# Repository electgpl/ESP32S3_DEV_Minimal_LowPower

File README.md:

# ESP32S3_DEV_Minimal_LowPower

This project implements a **minimal low-power development board** based on the **ESP32-S3**.  
The design focuses on reducing component count, board complexity, and idle power consumption, while still exposing the full capabilities of the ESP32-S3 for advanced development.  

Unlike traditional development boards, this design does **not include a USB-to-UART bridge**. Instead, it leverages the **native USB interface** of the ESP32-S3 for programming and communication, resulting in a simpler and more efficient design.  

---

## 🔑 Features

- **ESP32-S3 MCU** with external **QSPI Flash memory**.  
- **Native USB 2.0 interface** used for flashing and serial communication.  
- **MCP1826S LDO regulator**:  
  - Low quiescent current (IQ) for low-power operation.  
  - Stable supply for ESP32-S3 core.  
- **4-layer PCB**:  
  - Designed and manufactured at **NextPCB (PCBA service)**.  
  - Optimized for **low EMI/EMC compliance**.  
- **Castellated edges** for easy integration into other projects.  
- **Full pinout exposure**:  
  - All ESP32-S3 GPIOs available, including those not accessible on standard WROOM modules.  
  - Enables advanced use cases and maximum flexibility.  
- **On-board PCB antenna (MIFA type)**:  
  - Designed with **uSimmics EM simulation**.  
  - Verified radiation characteristics, dispersion parameters, and stack-up effects.  

---

## 📂 Repository structure

- **/schematic/** → Circuit schematic files.  
- **/pcb/** → PCB layout and Gerber files.  
- **/doc/** → Antenna simulation results and design notes.  
- **/firmware/** → Demo applications and example projects.  
- **/img/** → PCB renders and prototype photos.  

---

## 🧪 Demo Application

Included with this project is a **human presence detection demo** based on Wi-Fi spectral footprint analysis:  

- Scans available Wi-Fi networks, collecting **SSID** and **RSSI** values.  
- Applies a **probability-based algorithm** using **normal distribution** to estimate environmental changes.  
- Detects human presence based on variations in the Wi-Fi spectrum.  
- Displays results on a **color IPS display**.  

This demonstrates the potential of the ESP32-S3 in **low-cost sensing and AIoT applications** without requiring dedicated motion sensors.  

---

## 🔧 Typical applications

- Low-power IoT node development.  
- Integration into custom PCBs via castellated module design.  
- Edge-AI and machine learning applications.  
- Antenna research and RF prototyping.  

---

## 📑 References

- [ESP32-S3 Technical Reference Manual (Espressif)](https://www.espressif.com/en/support/download/technical-documents)  
- [MCP1826S LDO Datasheet (Microchip)](https://ww1.microchip.com/downloads/en/DeviceDoc/22057B.pdf)  
- [uSimmics EM Simulation Software](https://www.usimmics.com/)  

---

## 📸 Project preview

*(Insert here PCB renders, antenna simulation plots, and prototype photos)*  

---

## ⚖️ License

This project is released under the **MIT License**.  
You are free to use, modify, and distribute it, provided that proper credit is given.  

---

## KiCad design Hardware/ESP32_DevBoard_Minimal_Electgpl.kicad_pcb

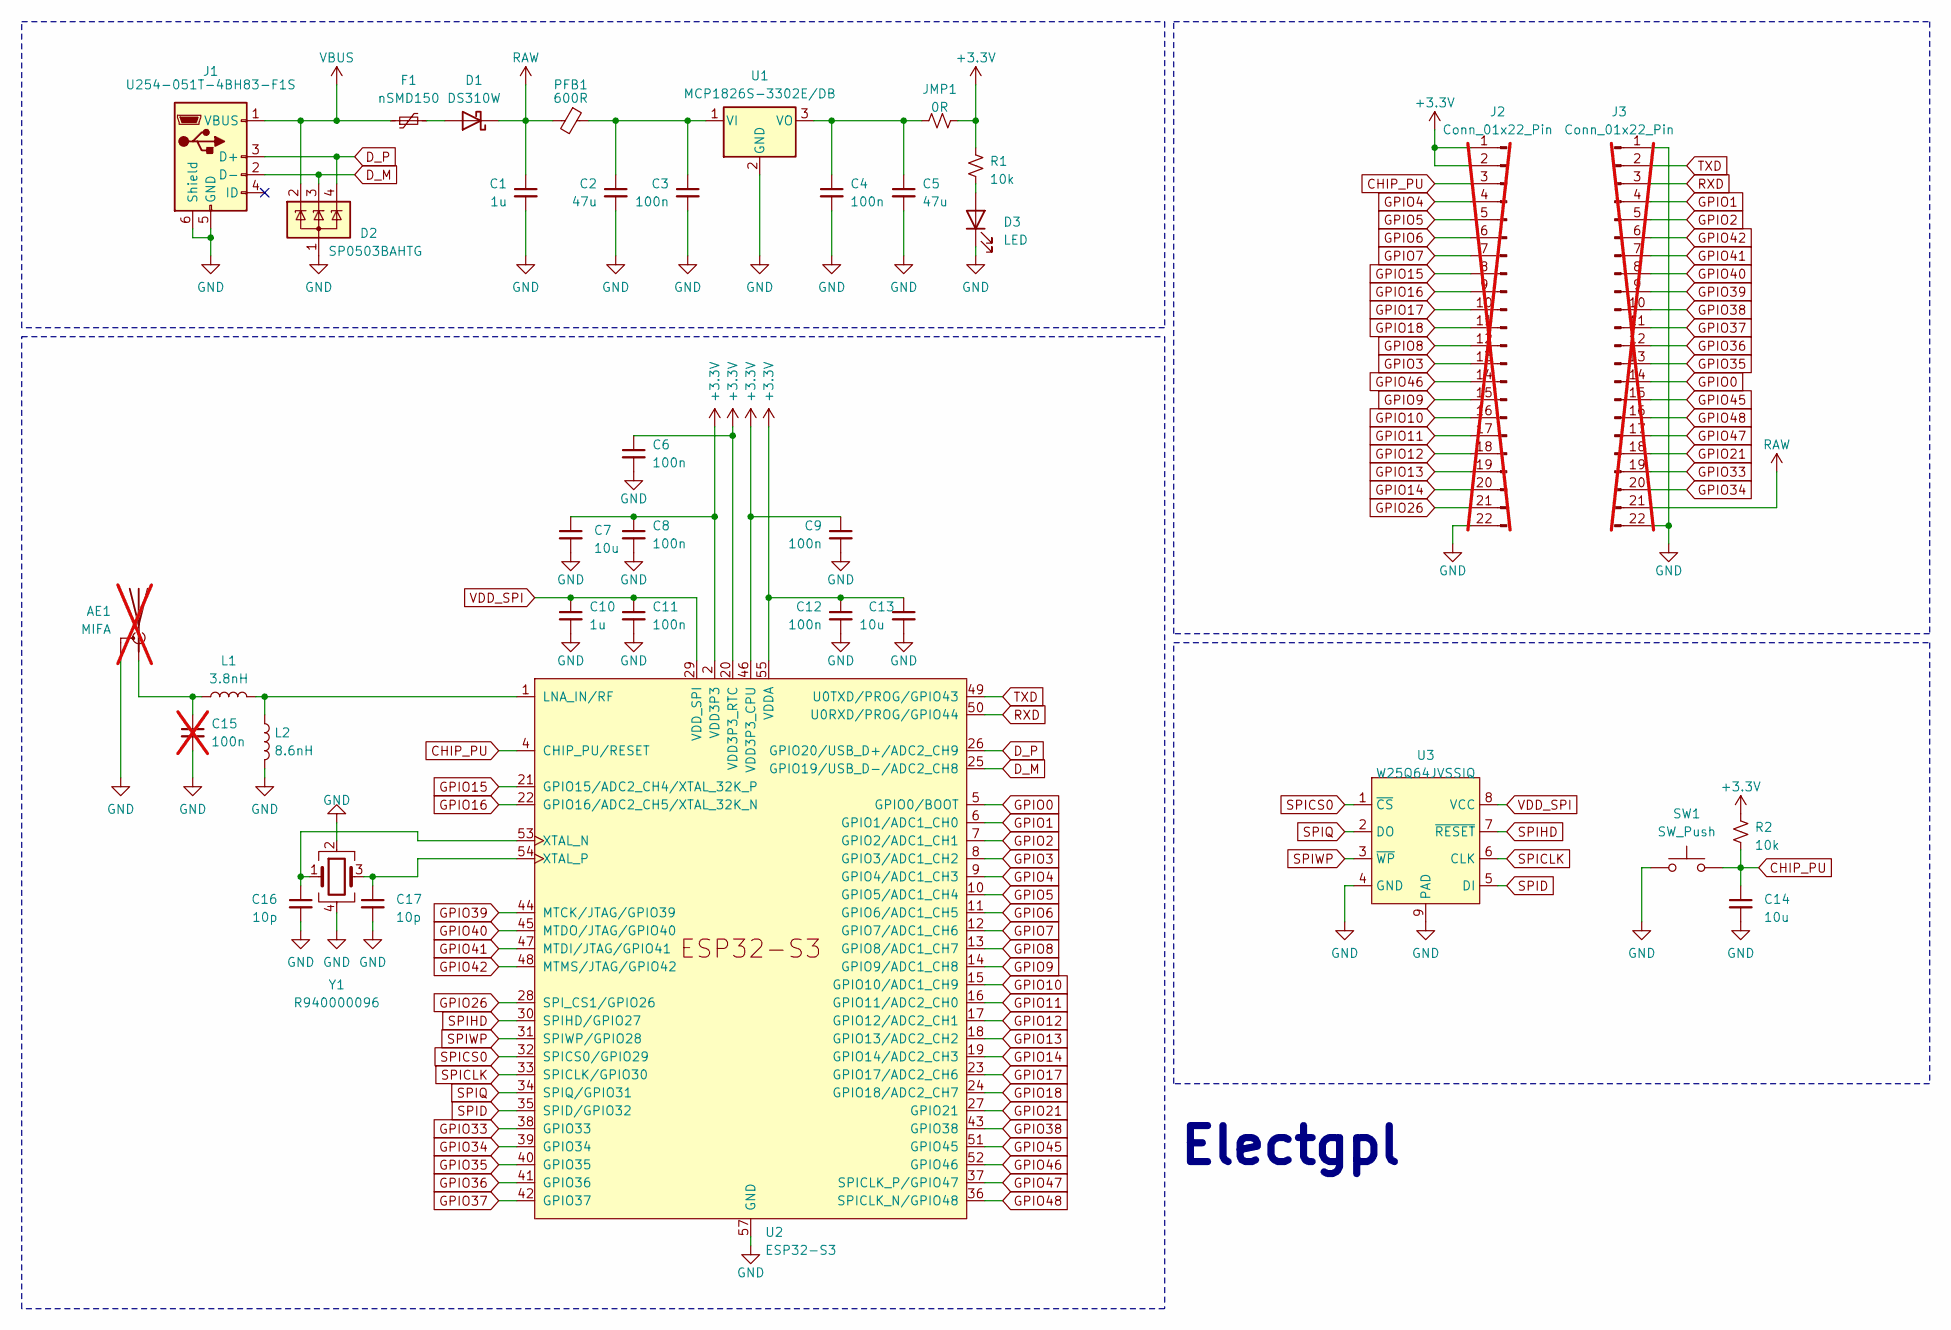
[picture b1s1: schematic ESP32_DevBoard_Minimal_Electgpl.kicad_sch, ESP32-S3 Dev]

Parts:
AE1: MIFA; ESPRESSIF_ESP32_MIFA_2.4GHz_Right; not fitted
C1, C10: 1u; C_0402_1005Metric; MFR P/N CL05X105KP5NNNC; LCSC CA0157860
C2, C5: 47u; C_0603_1608Metric; MFR P/N GRM188R60J476ME15D; LCSC CA0135493
C3, C4, C6, C8, C9, C11, C12: 100n; C_0402_1005Metric; MFR P/N CC0402KRX7R9BB104; LCSC RE0187778
C7, C13, C14: 10u; C_0603_1608Metric; MFR P/N GCM188D70J106ME36D; LCSC CA0384128
C15: 100n; C_0402_1005Metric; not fitted
C16, C17: 10p; C_0402_1005Metric; MFR P/N GRM1555C1H100GA01D; LCSC CA0137027
D1: DS310W; D_SOD-123; MFR P/N DS310W; LCSC DS0182252
D2: SP0503BAHTG; SOT-143; MFR P/N SP0503BAHTG; LCSC CP0003989
D3: LED; LED_0603_1608Metric; MFR P/N TJ-S1608B06HQYJY-A3; LCSC PH0093820
F1: nSMD150; Fuse_1206_3216Metric_Pad1.42x1.75mm_HandSolder; MFR P/N nSMD075-16V; LCSC CP0107097
J1: U254-051T-4BH83-F1S; USB_Micro-B_XKB_U254-051T-4BH83-F1S; MFR P/N U254-051T-4BH83-F1S; LCSC CO0893195
J2, J3: Conn_01x22_Pin; PinHeader_1x22_P2.54mm_Vertical; not fitted
JMP1: 0R; R_0603_1608Metric; MFR P/N AC0603JR-070RL; LCSC RE0030890
L1: 3.8nH; C_0402_1005Metric; MFR P/N SCC1005C4N3SSP; LCSC IN0076375
L2: 8.6nH; C_0402_1005Metric; MFR P/N SCW1005C8N2JST; LCSC IN0074484
PFB1: 600R; C_0603_1608Metric; MFR P/N BLM18SG331TN1D; LCSC WF0011783
R1, R2: 10k; R_0402_1005Metric; MFR P/N RC0402JR-0710KL; LCSC RE0023874
SW1: SW_Push; SW_Push_SPST_NO_Alps_SKRK; MFR P/N SKRKAEE020; LCSC SW0049182
U1: MCP1826S-3302E/DB; SOT-223; MFR P/N MCP1826S-3302E/DB; LCSC IC0133633
U2: ESP32-S3; QFN-56-1EP_7x7mm_P0.4mm_EP5.6x5.6mm; MFR P/N ESP32-S3R8; LCSC RF15788811
U3: W25Q64JVSSIQ; SOP-8_5.28x5.23mm_P1.27mm; MFR P/N GD25Q64ESIG; LCSC IC0447018
Y1: R940000096; Crystal_SMD_2016-4Pin_2.0x1.6mm; MFR P/N TAXM40M4ZHBCDT2T; LCSC C7206306

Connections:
+3.3V: C6.1, C7.1, C8.1, C9.1, C12.1, C13.1, J2.1, J2.2, JMP1.2, R1.1, R2.1, U2.2 (VDD3P3), U2.3 (VDD3P3), U2.20 (VDD3P3_RTC), U2.46 (VDD3P3_CPU), U2.55 (VDDA), U2.56 (VDDA)
CHIP_PU: C14.1, J2.3, R2.2, SW1.2, U2.4 (CHIP_PU/RESET)
D_M: D2.3 (K), J1.2 (D-), U2.25 (GPIO19/USB_D-/ADC2_CH8)
D_P: D2.4 (K), J1.3 (D+), U2.26 (GPIO20/USB_D+/ADC2_CH9)
GND: AE1.2 (Shield), C1.2, C2.2, C3.2, C4.2, C5.2, C6.2, C7.2, C8.2, C9.2, C10.2, C11.2, C12.2, C13.2, C14.2, C15.2, C16.2, C17.2, D2.1 (A), D3.1 (K), J1.5 (GND), J1.6 (Shield), J2.22, J3.1, J3.22, L2.2, SW1.1, U1.2 (GND), U2.57 (GND), U3.4 (GND), U3.9 (PAD), Y1.2, Y1.4
GPIO0: J3.14, U2.5 (GPIO0/BOOT)
GPIO1: J3.4, U2.6 (GPIO1/ADC1_CH0)
GPIO2: J3.5, U2.7 (GPIO2/ADC1_CH1)
GPIO3: J2.13, U2.8 (GPIO3/ADC1_CH2)
GPIO4: J2.4, U2.9 (GPIO4/ADC1_CH3)
GPIO5: J2.5, U2.10 (GPIO5/ADC1_CH4)
GPIO6: J2.6, U2.11 (GPIO6/ADC1_CH5)
GPIO7: J2.7, U2.12 (GPIO7/ADC1_CH6)
GPIO8: J2.12, U2.13 (GPIO8/ADC1_CH7)
GPIO9: J2.15, U2.14 (GPIO9/ADC1_CH8)
GPIO10: J2.16, U2.15 (GPIO10/ADC1_CH9)
GPIO11: J2.17, U2.16 (GPIO11/ADC2_CH0)
GPIO12: J2.18, U2.17 (GPIO12/ADC2_CH1)
GPIO13: J2.19, U2.18 (GPIO13/ADC2_CH2)
GPIO14: J2.20, U2.19 (GPIO14/ADC2_CH3)
GPIO15: J2.8, U2.21 (GPIO15/ADC2_CH4/XTAL_32K_P)
GPIO16: J2.9, U2.22 (GPIO16/ADC2_CH5/XTAL_32K_N)
GPIO17: J2.10, U2.23 (GPIO17/ADC2_CH6)
GPIO18: J2.11, U2.24 (GPIO18/ADC2_CH7)
GPIO21: J3.18, U2.27 (GPIO21)
GPIO26: J2.21, U2.28 (SPI_CS1/GPIO26)
GPIO33: J3.19, U2.38 (GPIO33)
GPIO34: J3.20, U2.39 (GPIO34)
GPIO35: J3.13, U2.40 (GPIO35)
GPIO36: J3.12, U2.41 (GPIO36)
GPIO37: J3.11, U2.42 (GPIO37)
GPIO38: J3.10, U2.43 (GPIO38)
GPIO39: J3.9, U2.44 (MTCK/JTAG/GPIO39)
GPIO40: J3.8, U2.45 (MTDO/JTAG/GPIO40)
GPIO41: J3.7, U2.47 (MTDI/JTAG/GPIO41)
GPIO42: J3.6, U2.48 (MTMS/JTAG/GPIO42)
GPIO45: J3.15, U2.51 (GPIO45)
GPIO46: J2.14, U2.52 (GPIO46)
GPIO47: J3.17, U2.37 (SPICLK_P/GPIO47)
GPIO48: J3.16, U2.36 (SPICLK_N/GPIO48)
unnamed: AE1.1 (A), C15.1, L1.1
unnamed: D1.2 (A), F1.2
unnamed: D3.2 (A), R1.2
unnamed: C2.1, C3.1, PFB1.1, U1.1 (VI)
unnamed: C4.1, C5.1, JMP1.1, U1.3 (VO)
unnamed: L1.2, L2.1, U2.1 (LNA_IN/RF)
unnamed: C16.1, U2.53 (XTAL_N), Y1.1
unnamed: C17.1, U2.54 (XTAL_P), Y1.3
RAW: C1.1, D1.1 (K), J3.21, PFB1.2
RXD: J3.3, U2.50 (U0RXD/PROG/GPIO44)
SPICLK: U2.33 (SPICLK/GPIO30), U3.6 (CLK)
SPICS0: U2.32 (SPICS0/GPIO29), U3.1 (~CS)
SPID: U2.35 (SPID/GPIO32), U3.5 (DI)
SPIHD: U2.30 (SPIHD/GPIO27), U3.7 (~RESET)
SPIQ: U2.34 (SPIQ/GPIO31), U3.2 (DO)
SPIWP: U2.31 (SPIWP/GPIO28), U3.3 (~WP)
TXD: J3.2, U2.49 (U0TXD/PROG/GPIO43)
VBUS: D2.2 (K), F1.1, J1.1 (VBUS)
VDD_SPI: C10.1, C11.1, U2.29 (VDD_SPI), U3.8 (VCC)

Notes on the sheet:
Electgpl

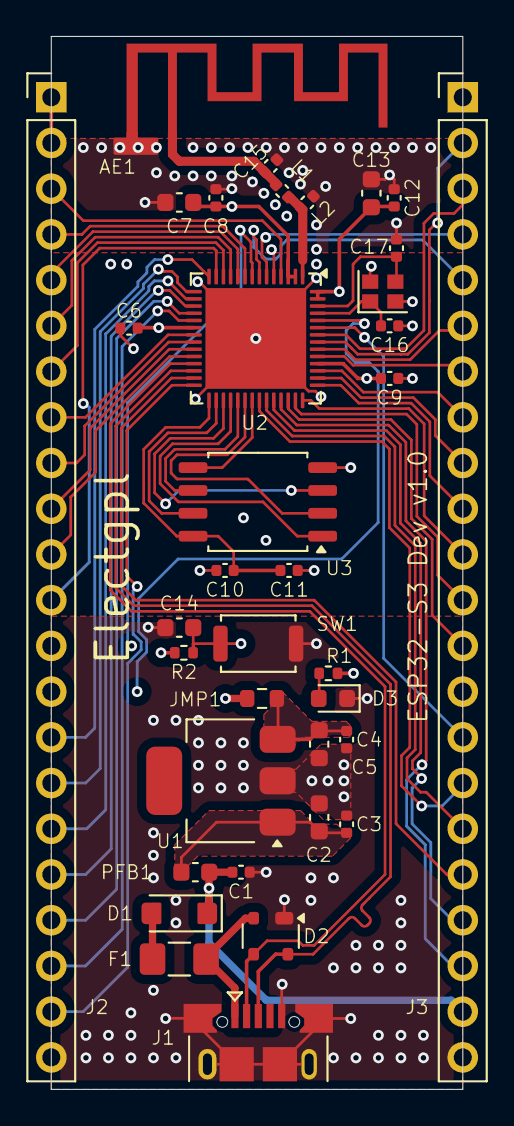
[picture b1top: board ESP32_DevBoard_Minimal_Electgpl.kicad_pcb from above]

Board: 4 copper layers, 22.9 x 58.5 mm, 36 parts (0 on the bottom side), 59 nets.
